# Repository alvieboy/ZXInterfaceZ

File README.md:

# ZX Interface Z

Interface Z - an expansion card for the ZX Spectrum which supports

- VGA Output
- USB devices such as joysticks, flash drives and keyboards
- Networking and Wifi
- Micro SD Card
- YM2149 audio

_Project status: Currently under development and only suitable for people that want
to help out with development and testing._

Current version is _ALPHA1_.

See [FEATURES](docs/FEATURES.md) for more details on the _ZX Interface Z_ features.
[(click here for PDF document)](docs/FEATURES.md.pdf)

# Overview

Block diagram of Interface Z [diagram](https://raw.githubusercontent.com/alvieboy/ZXInterfaceZ/master/docs/overview2.png)

# Models supported

The following models are supported:

- ZX Spectrum 16K
- ZX Spectrum 48K
- ZX Spectrum 128K (gray)
- ZX Spectrum 128K (toastrack)
- ZX Spectrum +2A
- ZX Spectrum +3

## Hardware
This section refers to the schematics and printed circuit board design of the Interface Z.
The digital design on the FPGA is described in the [FPGA design] section.
### Licensing
Schematics and PCB are released under [CC-BY-SA 2.0](https://creativecommons.org/licenses/by-sa/2.0/). This applies to all versions of the schematics and PCBs.
### Version
Current hardware version is 2.4. This is a pre-production version, not intented for general public availability.

## FPGA design
The FPGA design is written primarly in VHDL, targeting an Altera/Intel Cyclone IV device (EP4CE6E22C8N). There is no flash to store bitfile contents - the FPGA bitfile is loaded by the ESP32 MCU and stored inside the ESP32 flash.

### Licensing
Unless otherwise stated in each HDL or design support file, the FPGA design files are released under [BSD 3-Clause License](https://opensource.org/licenses/BSD-3-Clause).

## Firmware
This section applies to the firmware running on the ESP32 MCU.
### Licensing
Unless otherwise stated in each source support file, the firmware source files are released under [GPL version 3](https://opensource.org/licenses/GPL-3.0) license.

## Software
This section applies to the software intended to run on a separate computer (such as a PC, Mac or other).
### Licensing
Unless otherwise stated in each source support file, the software source files are released under [GPL version 3](https://opensource.org/licenses/GPL-3.0) license.

# Developing

See [DEVELOPING](docs/DEVELOPING.md) for development information regarding _ZX Interface Z_ 
[(click here for PDF document)](docs/DEVELOPING.md.pdf)

See [USER GUIDE](docs/USER_GUIDE.md) for build instructions.

# More information

- Follow the project on [Facebook - ZX Interface Z](https://www.facebook.com/zxinterfacez)
- Watch a [Demo of "Interface Z" for ZX Spectrum](https://www.youtube.com/watch?v=lMPc_8UKx1o) on YouTube

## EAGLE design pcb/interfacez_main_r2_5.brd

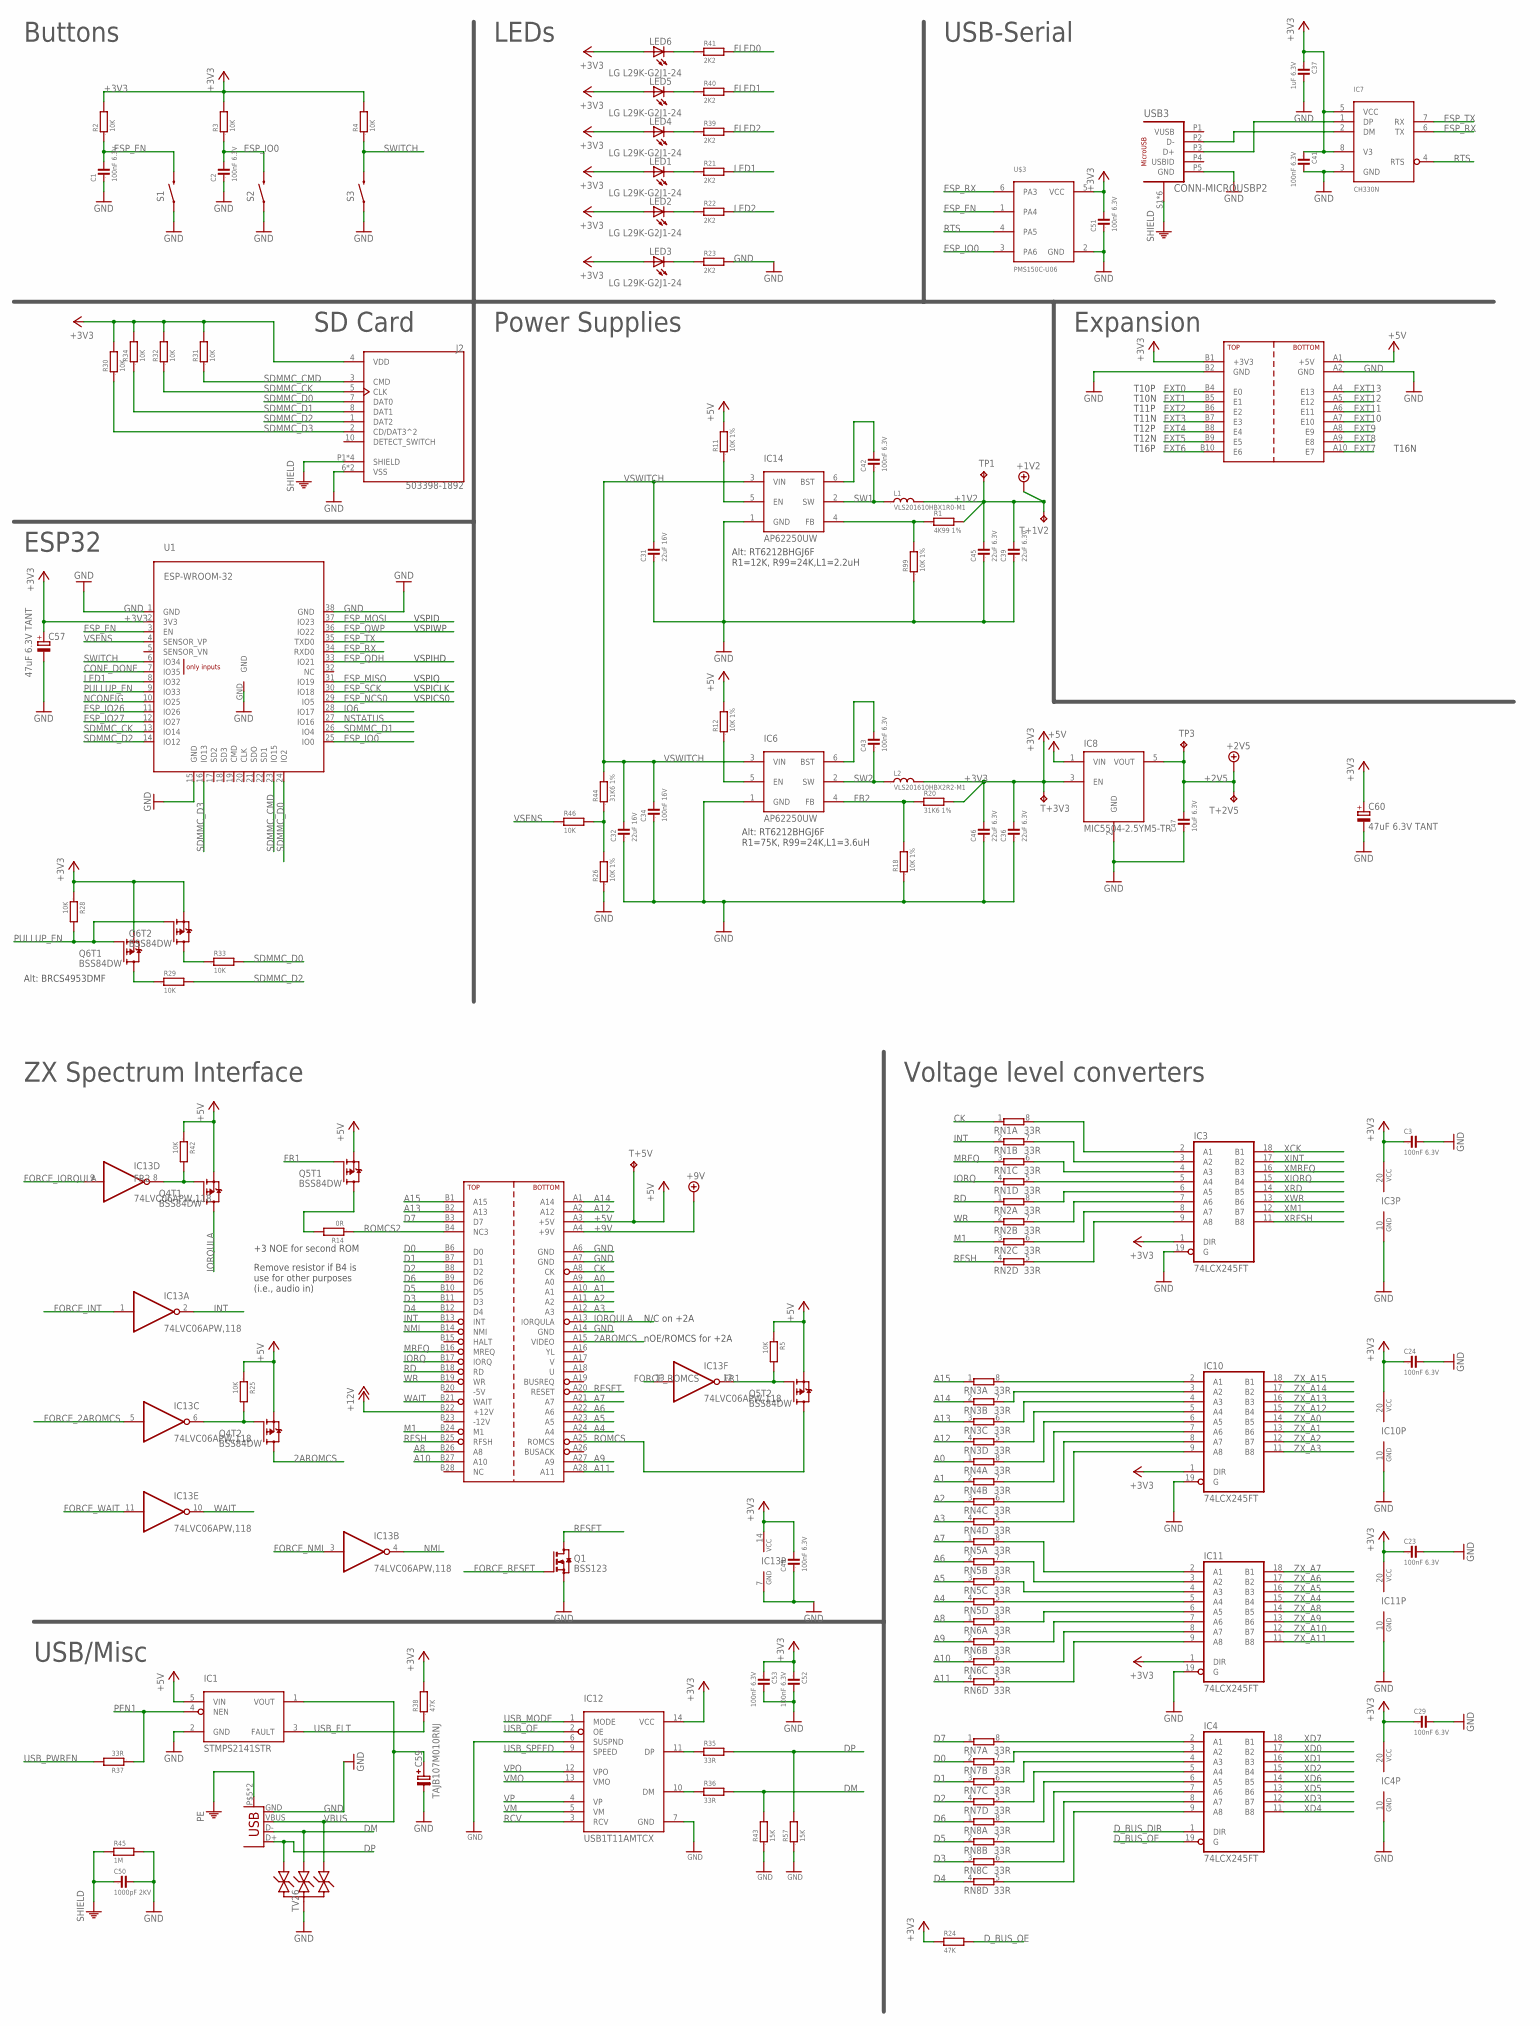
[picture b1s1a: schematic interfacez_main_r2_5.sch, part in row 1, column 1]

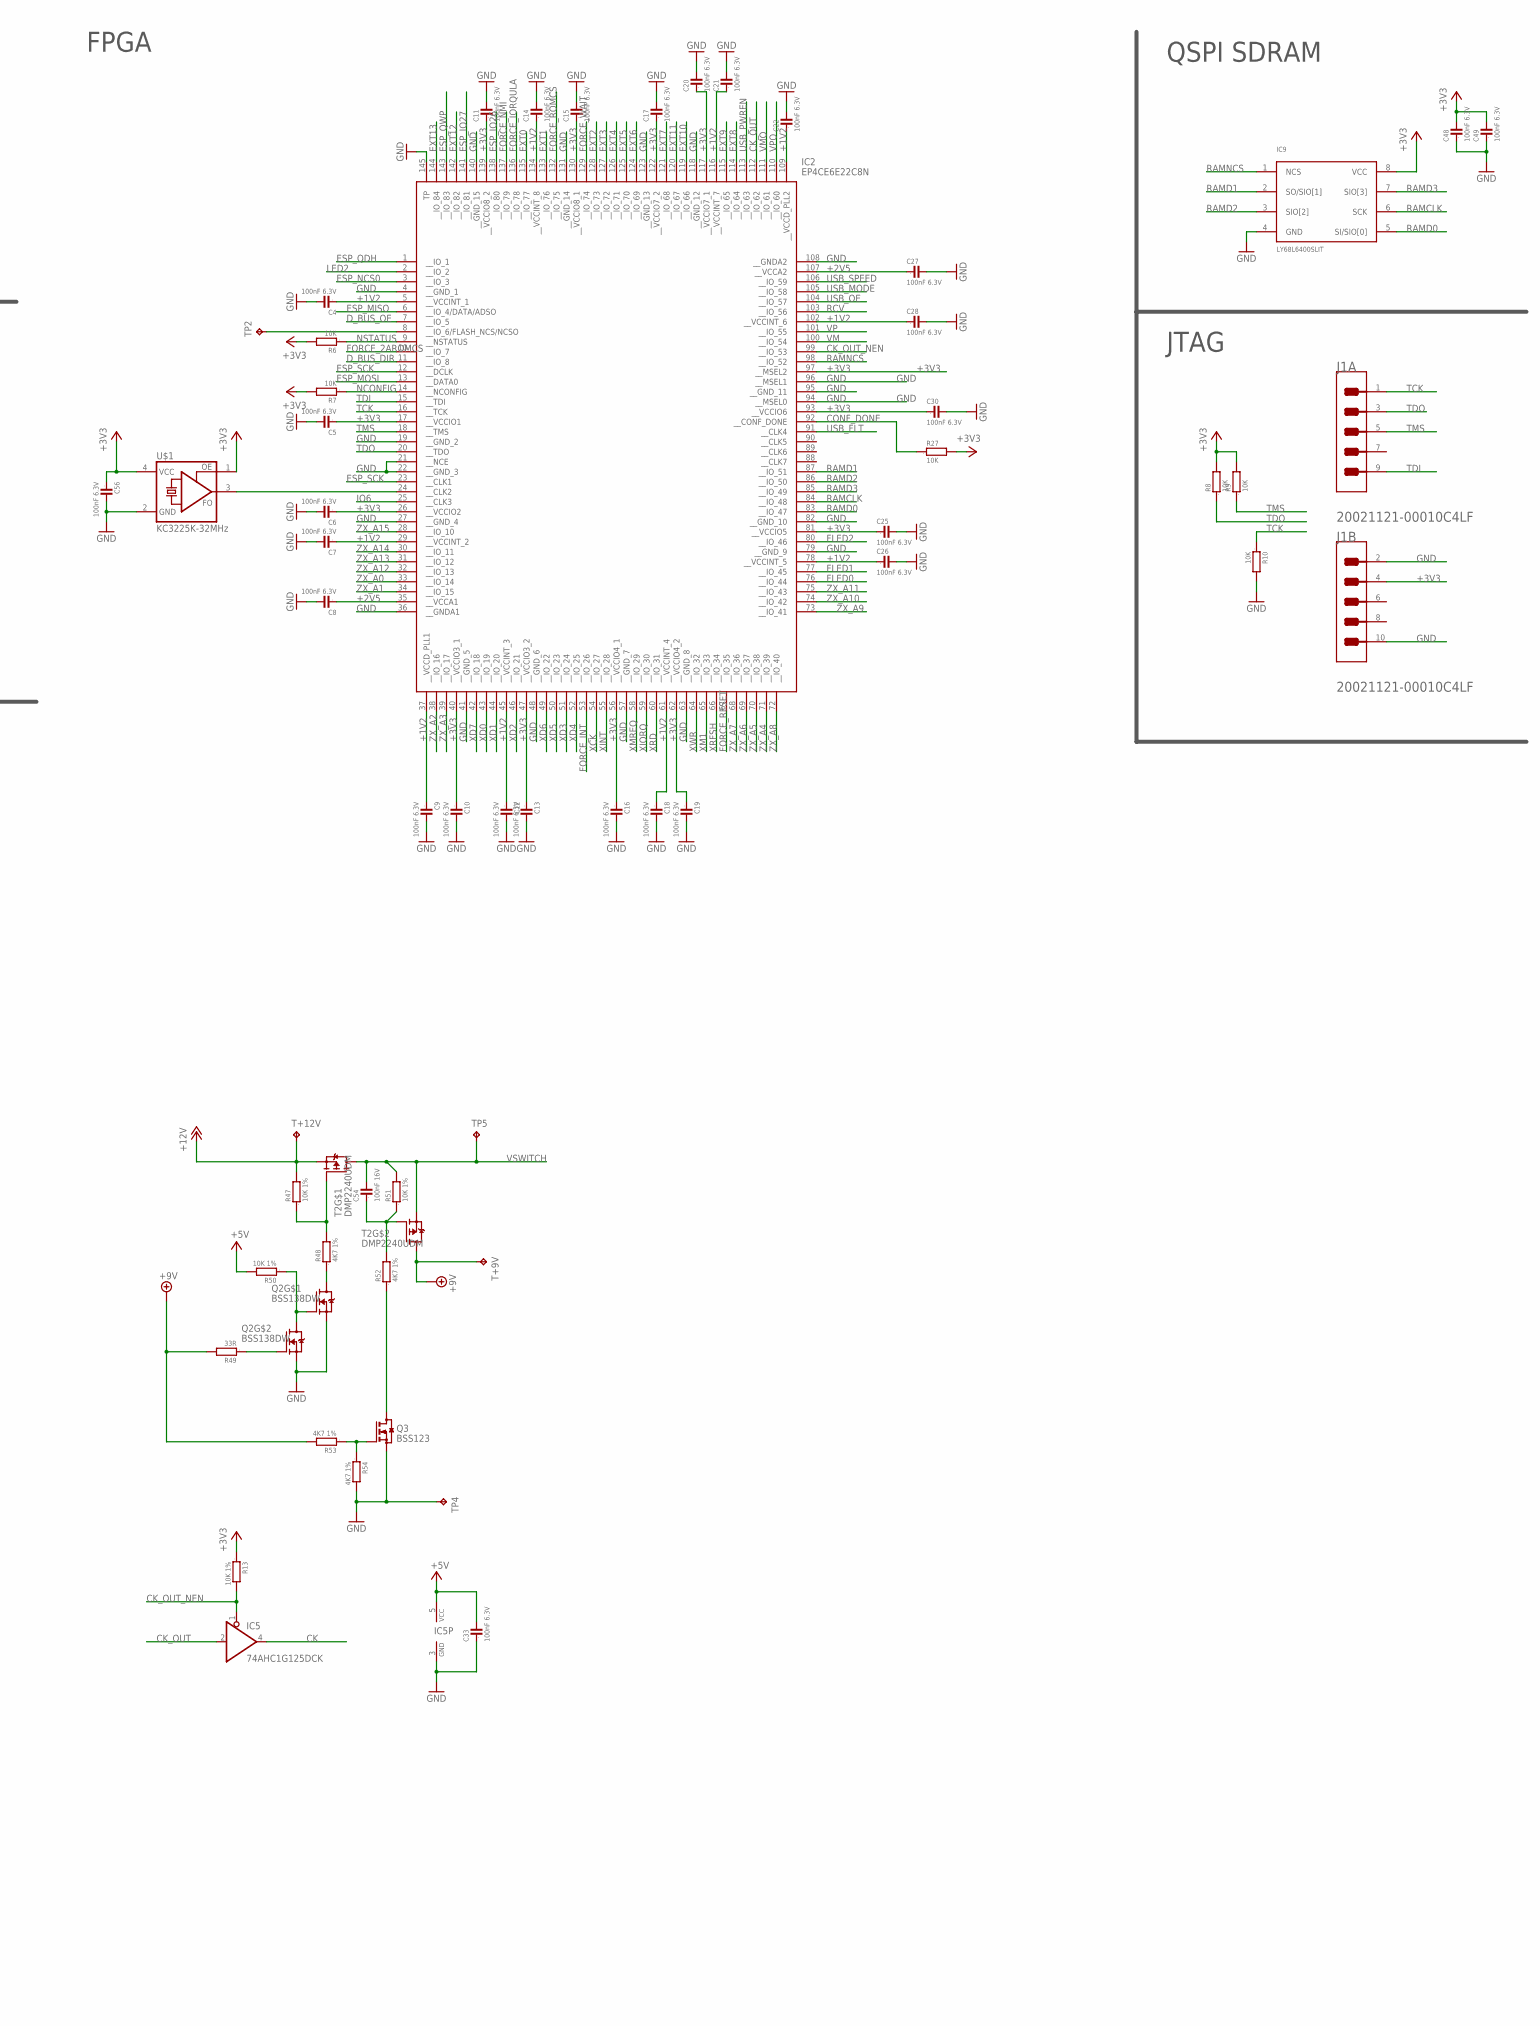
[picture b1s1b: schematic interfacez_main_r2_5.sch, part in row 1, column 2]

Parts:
C1, C2, C3, C4, C5, C6, C7, C8, C9, C10, C11, C12, C13, C14, C15, C16, C17, C18, C19, C20, C21, C22, C23, C24, C25, C26, C27, C28, C29, C30, C33, C40, C41, C42, C43, C48, C49, C51, C52, C53, C56: 100nF 6.3V; 0603
C31, C32: 22uF 16V; 1210
C34, C54: 100nF 16V; 0603
C36, C39, C45, C46: 22uF 6.3V; 0805
C37: 1uF 6.3V; 0603
C47: 10uF 6.3V; 0805
C50: 1000pF 2KV; 1210
C57, C60: 47uF 6.3V TANT; TANT_CASE_A
C59: TAJB107M010RNJ; TE-B-3528
CONN1: ZX_EDGE_DAUGHTERBOARD; ZX-EDGE-DAUGHTERBOARD
IC1: STMPS2141STR; SOT23-5L
IC2: EP4CE6E22C8N; QFP50P2200X2200X165-145N
IC3, IC4, IC10, IC11: 74LCX245FT; TSSOP20
IC5: 74AHC1G125DCK; SC70-5
IC6, IC14: AP62250UW; SOT23-6
IC7: CH330N; SOIC8
IC8: MIC5504-2.5YM5-TR; SOT23-5L
IC9: LY68L6400SLIT; SOIC8
IC12: USB1T11AMTCX; TSSOP14
IC13: 74LVC06APW,118; TSSOP14
J1: AMPHENOL_ICC_-_FCI_20021121-00010C4LFAMPHENOL_ICC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; AMPHENOL_ICC_-_FCI_20021121-00010C4LF_0
J2: 503398-1892; MOLEX_503398-1892
L1: VLS201610HBX1R0-M1; IND_0806
L2: VLS201610HBX2R2-M1; IND_0806
LED1, LED2, LED3, LED4, LED5, LED6: LG L29K-G2J1-24; LED-603
Q1, Q3: BSS123; SOT23
Q2: BSS138DW; SOT363_INFINEON
Q4, Q5, Q6: BSS84DW; SOT363_INFINEON
R1: 4K99 1%; 0603
R2, R3, R4, R5, R6, R7, R8, R9, R10, R25, R27, R28, R29, R30, R31, R32, R33, R34, R42, R46: 10K; 0603
R11, R12, R13, R18, R26, R47, R50, R51, R99: 10K 1%; 0603
R14: 0R; 0603
R20, R44: 31K6 1%; 0603
R21, R22, R23, R39, R40, R41: 2K2; 0603
R24, R38: 47K; 0603
R35, R36, R37, R49: 33R; 0603
R43, R57: 15K; 0603
R45: 1M; 0805
R48, R52, R53, R54: 4K7 1%; 0603
RN1, RN2, RN3, RN4, RN5, RN6, RN7, RN8: 33R; EXB28V
S1, S2, S3: SWITCHES_SMD-4; TACTILE_SWITCH_TALL
T2: DMP2240UDM; SOT23-6
T+1V2, T+2V5, T+3V3, T+5V, T+9V, T+12V: TPTP12SQ; TP12SQ
TP1, TP3: TPTP12R; TP12R
TP2, TP5: TPTP12SQ; TP12SQ
TP4: TPPAD1-13; P1-13
TV26: SP0503BAHT; SP0503
U1: ESP-WROOM-32
U$1: KC3225K-32MHz; KC3225K
U$3: PMS150C-U06; SOT23-6
U$5: INTERFACEZ_EDGEDAUGHTER; INTERFACEZ_EXPANSION_DAUGHTERCARD
USB2: USB-A-H
USB3: CONN-MICROUSBP2; MICROUSB_SMD_TH_7.5MM_4.85MM

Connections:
2AROMCS: CONN1.A15 (VIDEO), Q4.6 (D)
+1V2: C4.1, C7.1, C9.1, C12.1, C14.1, C18.1, C21.1, C22.1, C26.1, C28.1, C39.2, C45.2, IC2.5 (__VCCINT_1), IC2.29 (__VCCINT_2), IC2.37 (__VCCD_PLL1), IC2.45 (__VCCINT_3), IC2.61 (__VCCINT_4), IC2.78 (__VCCINT_5), IC2.102 (__VCCINT_6), IC2.109 (__VCCD_PLL2), IC2.116 (__VCCINT_7), IC2.134 (__VCCINT_8), L1.P$2 (2), R1.2, T+1V2.TP, TP1.TP
+2V5: C8.1, C27.1, C47.2, IC2.35 (__VCCA1), IC2.107 (__VCCA2), IC8.5 (VOUT), T+2V5.TP, TP3.TP
+3V3: C3.1, C5.1, C6.1, C10.1, C11.1, C13.1, C15.1, C16.1, C17.1, C19.1, C20.1, C23.1, C24.1, C25.1, C29.1, C30.1, C36.2, C37.1, C40.2, C41.1, C46.2, C48.2, C49.2, C51.2, C52.1, C53.1, C56.1, C57.PLUS (+), C60.PLUS (+), IC2.17 (__VCCIO1), IC2.26 (__VCCIO2), IC2.40 (__VCCIO3_1), IC2.47 (__VCCIO3_2), IC2.56 (__VCCIO4_1), IC2.62 (__VCCIO4_2), IC2.81 (__VCCIO5), IC2.93 (__VCCIO6), IC2.97 (__MSEL2), IC2.117 (__VCCIO7_1), IC2.122 (__VCCIO7_2), IC2.130 (__VCCIO8_1), IC2.139 (__VCCIO8_2), IC3.1 (DIR), IC3.20 (VCC), IC4.20 (VCC), IC7.5 (VCC), IC7.8 (V3), IC8.3 (EN), IC9.8 (VCC), IC10.1 (DIR), IC10.20 (VCC), IC11.1 (DIR), IC11.20 (VCC), IC12.14 (VCC), IC13.14 (VCC), J1.4, J2.4 (VDD), L2.P$2 (2), LED1.A, LED2.A, LED3.A, LED4.A, LED5.A, LED6.A, Q6.1 (S), Q6.4 (S), R2.2, R3.2, R4.2, R6.2, R7.2, R8.2, R9.2, R13.1, R20.2, R24.1, R27.2, R28.1, R30.2, R31.2, R32.2, R34.2, R38.2, T+3V3.TP, U1.2 (3V3), U$1.1 (OE), U$1.4 (VCC), U$3.5 (VCC), U$5.B1 (+3V3)
+5V: C33.2, CONN1.A3 (+5V), IC1.5 (VIN), IC5.5 (VCC), IC8.1 (VIN), Q4.1 (S), Q4.4 (S), Q5.1 (S), Q5.4 (S), R5.1, R11.2, R12.2, R25.1, R42.1, R50.2, T+5V.TP, U$5.A1 (+5V)
+9V: CONN1.A4 (+9V), R49.2, R53.2, T2.4 (D), T+9V.TP
+12V: CONN1.B22 (+12V), R47.2, T2.5 (S), T+12V.TP
-5V: CONN1.B20 (-5V)
-12V: CONN1.B23 (-12V)
A0: CONN1.A9 (A0), RN4.1
A1: CONN1.A10 (A1), RN4.2 (1)
A2: CONN1.A11 (A2), RN4.3 (1)
A3: CONN1.A12 (A3), RN4.4 (1)
A4: CONN1.A24 (A4), RN5.4 (1)
A5: CONN1.A23 (A5), RN5.3 (1)
A6: CONN1.A22 (A6), RN5.2 (1)
A7: CONN1.A21 (A7), RN5.1
A8: CONN1.B26 (A8), RN6.1
A9: CONN1.A27 (A9), RN6.2 (1)
A10: CONN1.B27 (A10), RN6.3 (1)
A11: CONN1.A28 (A11), RN6.4 (1)
A12: CONN1.A2 (A12), RN3.4 (1)
A13: CONN1.B2 (A13), RN3.3 (1)
A14: CONN1.A1 (A14), RN3.2 (1)
A15: CONN1.B1 (A15), RN3.1
CK: CONN1.A8 (CK), IC5.4 (O), RN1.1
CK_OUT: IC2.112 (__IO_62), IC5.2 (I)
CK_OUT_NEN: IC2.99 (__IO_53), IC5.1 (OE), R13.2
CONF_DONE: IC2.92 (__CONF_DONE), R27.1, U1.7 (IO35)
D0: CONN1.B6 (D0), RN7.2 (1)
D1: CONN1.B7 (D1), RN7.3 (1)
D2: CONN1.B8 (D2), RN7.4 (1)
D3: CONN1.B11 (D3), RN8.3 (1)
D4: CONN1.B12 (D4), RN8.4 (1)
D5: CONN1.B10 (D5), RN8.2 (1)
D6: CONN1.B9 (D6), RN8.1
D7: CONN1.B3 (D7), RN7.1
DM: R36.2, R43.2, TV26.3 (B), USB2.D-
DP: R35.2, R57.2, TV26.2 (A), USB2.D+
D_BUS_DIR: IC2.11 (__IO_8), IC4.1 (DIR)
D_BUS_OE: IC2.7 (__IO_5), IC4.19 (G), R24.2
ESP_EN: C1.2, R2.1, S1.B2 (2), U1.3 (EN), U$3.1 (PA4)
ESP_IO0: C2.2, R3.1, S2.B2 (2), U1.25 (IO0), U$3.3 (PA6)
ESP_IO26: IC2.138 (__IO_80), U1.11 (IO26)
ESP_IO27: IC2.141 (__IO_81), U1.12 (IO27)
ESP_MISO: IC2.6 (__IO_4/DATA/ADSO), U1.31 (IO19)
ESP_MOSI: IC2.13 (__DATA0), U1.37 (IO23)
ESP_NCS0: IC2.3 (__IO_3), U1.29 (IO5)
ESP_QDH: IC2.1 (__IO_1), U1.33 (IO21)
ESP_QWP: IC2.143 (__IO_83), U1.36 (IO22)
ESP_RX: IC7.6 (TX), U1.34 (RXD0), U$3.6 (PA3)
ESP_SCK: IC2.12 (__DCLK), IC2.23 (__CLK1), U1.30 (IO18)
ESP_TX: IC7.7 (RX), U1.35 (TXD0)
EXT0: IC2.135 (__IO_77), U$5.B4 (E0)
EXT1: IC2.133 (__IO_76), U$5.B5 (E1)
EXT2: IC2.128 (__IO_73), U$5.B6 (E2)
EXT3: IC2.127 (__IO_72), U$5.B7 (E3)
EXT4: IC2.126 (__IO_71), U$5.B8 (E4)
EXT5: IC2.125 (__IO_70), U$5.B9 (E5)
EXT6: IC2.124 (__IO_69), U$5.B10 (E6)
EXT7: IC2.121 (__IO_68), U$5.A10 (E7)
EXT8: IC2.114 (__IO_64), U$5.A9 (E8)
EXT9: IC2.115 (__IO_65), U$5.A8 (E9)
EXT10: IC2.119 (__IO_66), U$5.A7 (E10)
EXT11: IC2.120 (__IO_67), U$5.A6 (E11)
EXT12: IC2.142 (__IO_82), U$5.A5 (E12)
EXT13: IC2.144 (__IO_84), U$5.A4 (E13)
FB2: IC6.4 (FB), R18.2, R20.1
FLED0: IC2.76 (__IO_44), R41.2
FLED1: IC2.77 (__IO_45), R40.2
FLED2: IC2.80 (__IO_46), R39.2
FORCE_2AROMCS: IC2.10 (__IO_7), IC13.5 (I)
FORCE_INT: IC2.53 (__IO_26), IC13.1 (I)
FORCE_IORQULA: IC2.136 (__IO_78), IC13.9 (I)
FORCE_NMI: IC2.137 (__IO_79), IC13.3 (I)
FORCE_RESET: IC2.67 (__IO_35), Q1.1 (G)
FORCE_ROMCS: IC2.132 (__IO_75), IC13.13 (I)
FORCE_WAIT: IC2.129 (__IO_74), IC13.11 (I)
FR1: IC13.12 (O), Q5.2 (G), Q5.5 (G), R5.2
FR2: IC13.8 (O), Q4.5 (G), R42.2
GND: C1.1, C2.1, C3.2, C4.2, C5.2, C6.2, C7.2, C8.2, C9.2, C10.2, C11.2, C12.2, C13.2, C14.2, C15.2, C16.2, C17.2, C18.2, C19.2, C20.2, C21.2, C22.2, C23.2, C24.2, C25.2, C26.2, C27.2, C28.2, C29.2, C30.2, C31.1, C32.1, C33.1, C34.1, C36.1, C37.2, C39.1, C40.1, C41.2, C45.1, C46.1, C47.1, C48.1, C49.1, C50.2, C51.1, C52.2, C53.2, C56.2, C57.MINUS (-), C59.-, C60.MINUS (-), CONN1.A6 (GND), CONN1.A7 (GND), CONN1.A14 (GND), IC1.2 (GND), IC2.4 (__GND_1), IC2.19 (__GND_2), IC2.21 (__NCE), IC2.22 (__GND_3), IC2.27 (__GND_4), IC2.36 (__GNDA1), IC2.41 (__GND_5), IC2.48 (__GND_6), IC2.57 (__GND_7), IC2.63 (__GND_8), IC2.79 (__GND_9), IC2.82 (__GND_10), IC2.94 (__MSEL0), IC2.95 (__GND_11), IC2.96 (__MSEL1), IC2.108 (__GNDA2), IC2.118 (__GND_12), IC2.123 (__GND_13), IC2.131 (__GND_14), IC2.140 (__GND_15), IC2.145 (TP), IC3.10 (GND), IC3.19 (G), IC4.10 (GND), IC5.3 (GND), IC6.1 (GND), IC7.3 (GND), IC8.2 (GND), IC9.4 (GND), IC10.10 (GND), IC10.19 (G), IC11.10 (GND), IC11.19 (G), IC12.6 (SUSPND), IC12.7 (GND), IC13.7 (GND), IC14.1 (GND), J1.2, J1.10, J2.6 (VSS), J2.9 (VSS), Q1.2 (S), Q2.1 (S), Q2.4 (S), Q3.2 (S), R10.2, R18.1, R23.2, R26.1, R43.1, R45.2, R54.2, R57.1, R99.1, S1.A2 (1), S2.A2 (1), S3.A2 (1), TP4.TP, TV26.1 (COM), U1.1 (GND), U1.15 (GND), U1.38 (GND), U1.GND, U$1.2 (GND), U$3.2 (GND), U$5.A2 (GND), U$5.B2 (GND), USB2.GND, USB3.P5 (GND)
INT: CONN1.B13 (INT), IC13.2 (O), RN1.2 (1)
IO6: IC2.25 (__CLK3), U1.28 (IO17)
IORQ: CONN1.B17 (IORQ), RN1.4 (1)
IORQULA: CONN1.A13 (IORQULA), Q4.3 (D)
LED1: R21.2, U1.8 (IO32)
LED2: IC2.2 (__IO_2), R22.2
M1: CONN1.B24 (M1), RN2.3 (1)
MREQ: CONN1.B16 (MREQ), RN1.3 (1)
unnamed: Q5.3 (D), R14.2
unnamed: LED1.C, R21.1
unnamed: LED2.C, R22.1
unnamed: LED3.C, R23.1
unnamed: R47.1, R48.2, T2.1 (G)
unnamed: Q2.3 (D), R48.1
unnamed: IC3.2 (A1), RN1.8 (2)
unnamed: IC3.3 (A2), RN1.7 (2)
unnamed: IC10.2 (A1), RN3.8 (2)
unnamed: IC10.3 (A2), RN3.7 (2)
unnamed: IC10.4 (A3), RN3.6 (2)
unnamed: IC10.5 (A4), RN3.5 (2)
unnamed: IC2.24 (__CLK2), U$1.3 (FO)
unnamed: IC10.6 (A5), RN4.8 (2)
unnamed: IC10.7 (A6), RN4.7 (2)
unnamed: IC4.2 (A1), RN7.8 (2)
unnamed: IC4.3 (A2), RN7.7 (2)
unnamed: IC10.8 (A7), RN4.6 (2)
unnamed: IC2.8 (__IO_6/FLASH_NCS/NCSO), TP2.TP
unnamed: LED4.C, R39.1
unnamed: C43.2, IC6.6 (BST)
unnamed: IC10.9 (A8), RN4.5 (2)
unnamed: IC11.2 (A1), RN5.8 (2)
unnamed: IC11.3 (A2), RN5.7 (2)
unnamed: IC11.4 (A3), RN5.6 (2)
unnamed: IC11.5 (A4), RN5.5 (2)
unnamed: IC11.6 (A5), RN6.8 (2)
unnamed: IC11.7 (A6), RN6.7 (2)
unnamed: IC11.8 (A7), RN6.6 (2)
unnamed: IC11.9 (A8), RN6.5 (2)
unnamed: IC4.4 (A3), RN7.6 (2)
unnamed: IC4.5 (A4), RN7.5 (2)
unnamed: IC4.6 (A5), RN8.8 (2)
unnamed: IC4.7 (A6), RN8.7 (2)
unnamed: IC4.8 (A7), RN8.6 (2)
unnamed: IC4.9 (A8), RN8.5 (2)
unnamed: IC3.4 (A3), RN1.6 (2)
unnamed: IC3.5 (A4), RN1.5 (2)
unnamed: IC3.6 (A5), RN2.8 (2)
unnamed: IC3.7 (A6), RN2.7 (2)
unnamed: IC3.8 (A7), RN2.6 (2)
unnamed: IC3.9 (A8), RN2.5 (2)
unnamed: C42.2, IC14.6 (BST)
unnamed: IC6.5 (EN), R12.1
unnamed: IC14.4 (FB), R1.1, R99.2
unnamed: IC14.5 (EN), R11.1
unnamed: IC13.6 (O), Q4.2 (G), R25.2
unnamed: Q6.3 (D), R29.1
unnamed: LED5.C, R40.1
unnamed: LED6.C, R41.1
unnamed: IC12.11 (DP), R35.1
unnamed: IC12.10 (DM), R36.1
unnamed: Q2.5 (G), Q2.6 (D), R50.1
unnamed: Q6.6 (D), R33.1
unnamed: Q2.2 (G), R49.1
unnamed: C54.1, R51.1, R52.2, T2.3 (G)
unnamed: Q3.1 (G), R53.1, R54.1
unnamed: Q3.3 (D), R52.1
unnamed: IC7.1 (DP), USB3.P3 (D+)
unnamed: IC7.2 (DM), USB3.P2 (D-)
NCONFIG: IC2.14 (__NCONFIG), R7.1, U1.10 (IO25)
NMI: CONN1.B14 (NMI), IC13.4 (O)
NSTATUS: IC2.9 (__NSTATUS), R6.1, U1.27 (IO16)
PE: C50.1, J2.P1 (SHIELD), J2.P2 (SHIELD), J2.P3 (SHIELD), J2.P4 (SHIELD), R45.1, USB2.P$5 (SHIELD), USB2.P$6 (SHIELD), USB3.S1 (SHIELD), USB3.S2 (SHIELD), USB3.S3 (SHIELD), USB3.S4 (SHIELD), USB3.S5 (SHIELD), USB3.S6 (SHIELD)
PEN1: IC1.4 (NEN), R37.1
PULLUP_EN: Q6.2 (G), Q6.5 (G), R28.2, U1.9 (IO33)
RAMCLK: IC2.84 (__IO_48), IC9.6 (SCK)
RAMD0: IC2.83 (__IO_47), IC9.5 (SI/SIO[0])
RAMD1: IC2.87 (__IO_51), IC9.2 (SO/SIO[1])
RAMD2: IC2.86 (__IO_50), IC9.3 (SIO[2])
RAMD3: IC2.85 (__IO_49), IC9.7 (SIO[3])
RAMNCS: IC2.98 (__IO_52), IC9.1 (NCS)
RCV: IC2.103 (__IO_56), IC12.3 (RCV)
RD: CONN1.B18 (RD), RN2.1
RESET: CONN1.A20 (RESET), Q1.3 (D)
RFSH: CONN1.B25 (RFSH), RN2.4 (1)
ROMCS: CONN1.A25 (ROMCS), Q5.6 (D)
ROMCS2: CONN1.B4 (NC3), R14.1
RTS: IC7.4 (RTS), U$3.4 (PA5)
SDMMC_CK: J2.5 (CLK), R32.1, U1.13 (IO14)
SDMMC_CMD: J2.3 (CMD), R31.1, U1.23 (IO15)
SDMMC_D0: J2.7 (DAT0), R33.2, U1.24 (IO2)
SDMMC_D1: J2.8 (DAT1), R34.1, U1.26 (IO4)
SDMMC_D2: J2.1 (DAT2), R29.2, U1.14 (IO12)
SDMMC_D3: J2.2 (CD/DAT3^2), R30.1, U1.16 (IO13)
SW1: C42.1, IC14.2 (SW), L1.P$1 (1)
SW2: C43.1, IC6.2 (SW), L2.P$1 (1)
SWITCH: R4.1, S3.B2 (2), U1.6 (IO34)
TCK: IC2.16 (__TCK), J1.1, R10.1
TDI: IC2.15 (__TDI), J1.9
TDO: IC2.20 (__TDO), J1.3, R8.1
TMS: IC2.18 (__TMS), J1.5, R9.1
USB_FLT: IC1.3 (FAULT), IC2.91 (__CLK4), R38.1
USB_MODE: IC2.105 (__IO_58), IC12.1 (MODE)
USB_OE: IC2.104 (__IO_57), IC12.2 (OE)
USB_PWREN: IC2.113 (__IO_63), R37.2
USB_SPEED: IC2.106 (__IO_59), IC12.9 (SPEED)
VBUS: C59.+, IC1.1 (VOUT), TV26.4 (C), USB2.VBUS
VDIV: R26.2, R44.1, R46.2
VM: IC2.100 (__IO_54), IC12.5 (VM)
VMO: IC2.111 (__IO_61), IC12.13 (VMO)
VP: IC2.101 (__IO_55), IC12.4 (VP)
VPO: IC2.110 (__IO_60), IC12.12 (VPO)
VSENS: R46.1, U1.4 (SENSOR_VP)
VSWITCH: C31.2, C32.2, C34.2, C54.2, IC6.3 (VIN), IC14.3 (VIN), R44.2, R51.2, T2.2 (S), T2.6 (D), TP5.TP
WAIT: CONN1.B21 (WAIT), IC13.10 (O)
WR: CONN1.B19 (WR), RN2.2 (1)
XCK: IC2.54 (__IO_27), IC3.18 (B1)
XD0: IC2.43 (__IO_19), IC4.17 (B2)
XD1: IC2.44 (__IO_20), IC4.16 (B3)
XD2: IC2.46 (__IO_21), IC4.15 (B4)
XD3: IC2.51 (__IO_24), IC4.12 (B7)
XD4: IC2.52 (__IO_25), IC4.11 (B8)
XD5: IC2.50 (__IO_23), IC4.13 (B6)
XD6: IC2.49 (__IO_22), IC4.14 (B5)
XD7: IC2.42 (__IO_18), IC4.18 (B1)
XINT: IC2.55 (__IO_28), IC3.17 (B2)
XIORQ: IC2.59 (__IO_30), IC3.15 (B4)
XM1: IC2.65 (__IO_33), IC3.12 (B7)
XMREQ: IC2.58 (__IO_29), IC3.16 (B3)
XRD: IC2.60 (__IO_31), IC3.14 (B5)
XRFSH: IC2.66 (__IO_34), IC3.11 (B8)
XWR: IC2.64 (__IO_32), IC3.13 (B6)
ZX_A0: IC2.33 (__IO_14), IC10.14 (B5)
ZX_A1: IC2.34 (__IO_15), IC10.13 (B6)
ZX_A2: IC2.38 (__IO_16), IC10.12 (B7)
ZX_A3: IC2.39 (__IO_17), IC10.11 (B8)
ZX_A4: IC2.71 (__IO_39), IC11.15 (B4)
ZX_A5: IC2.70 (__IO_38), IC11.16 (B3)
ZX_A6: IC2.69 (__IO_37), IC11.17 (B2)
ZX_A7: IC2.68 (__IO_36), IC11.18 (B1)
ZX_A8: IC2.72 (__IO_40), IC11.14 (B5)
ZX_A9: IC2.73 (__IO_41), IC11.13 (B6)
ZX_A10: IC2.74 (__IO_42), IC11.12 (B7)
ZX_A11: IC2.75 (__IO_43), IC11.11 (B8)
ZX_A12: IC2.32 (__IO_13), IC10.15 (B4)
ZX_A13: IC2.31 (__IO_12), IC10.16 (B3)
ZX_A14: IC2.30 (__IO_11), IC10.17 (B2)
ZX_A15: IC2.28 (__IO_10), IC10.18 (B1)

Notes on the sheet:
Buttons
SD Card
ESP32
LEDs
USB-Serial
Power Supplies
FPGA
QSPI SDRAM
ZX Spectrum Interface
Voltage level converters
USB/Misc
VSPICLK
VSPICS0
VSPIQ
VSPIWP
VSPIHD
VSPID
+3 NOE for second ROM
Alt: BRCS4953DMF
Expansion
T10P
T10N
T11P
T11N
T12P
T12N
T16P
T16N
JTAG
N/C on +2A
nOE/ROMCS for +2A
Remove resistor if B4 is use for other purposes (i.e., audio in)
Alt: RT6212BHGJ6F R1=12K, R99=24K,L1=2.2uH
Alt: RT6212BHGJ6F R1=75K, R99=24K,L1=3.6uH

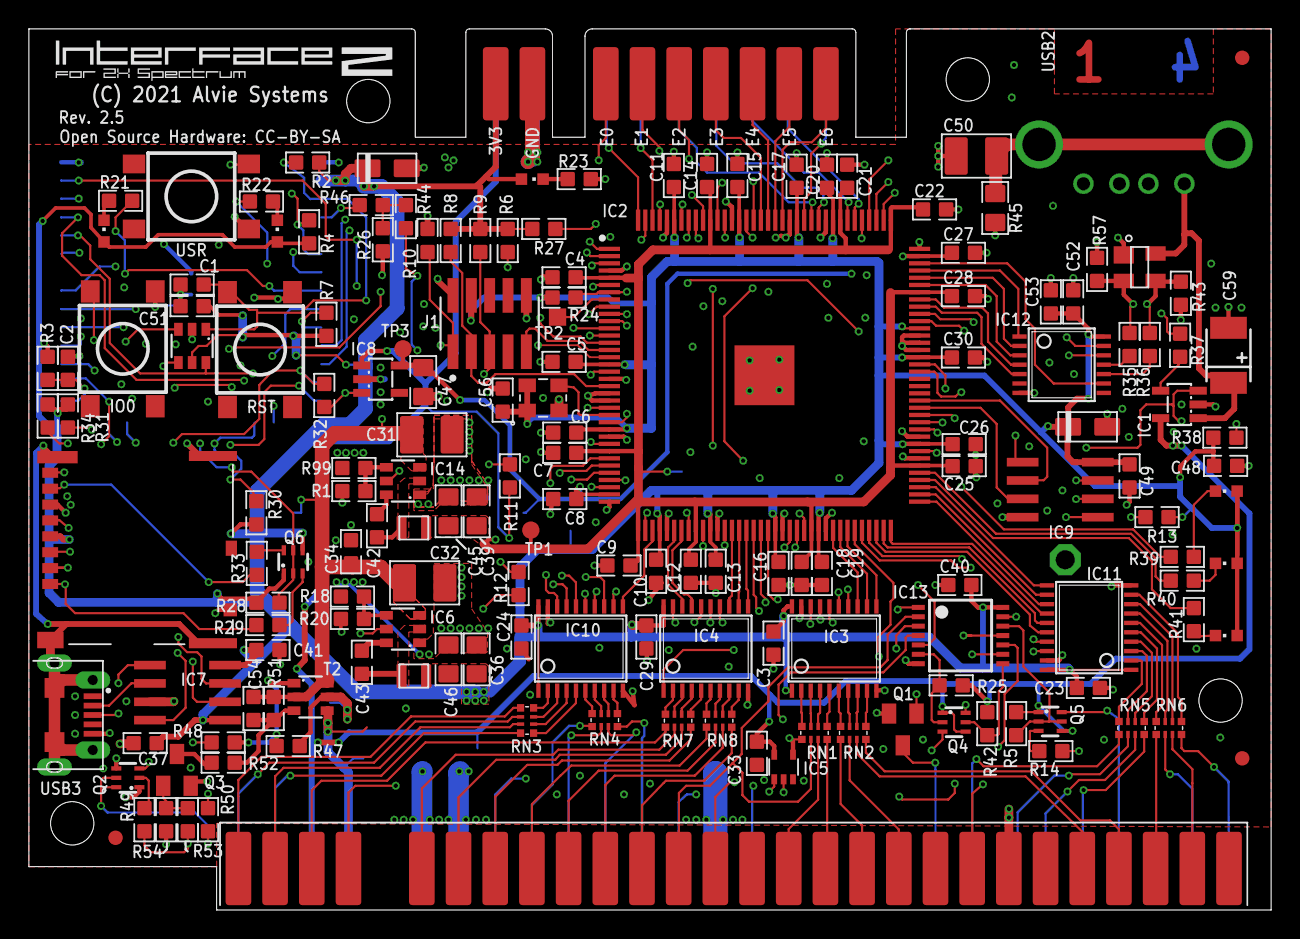
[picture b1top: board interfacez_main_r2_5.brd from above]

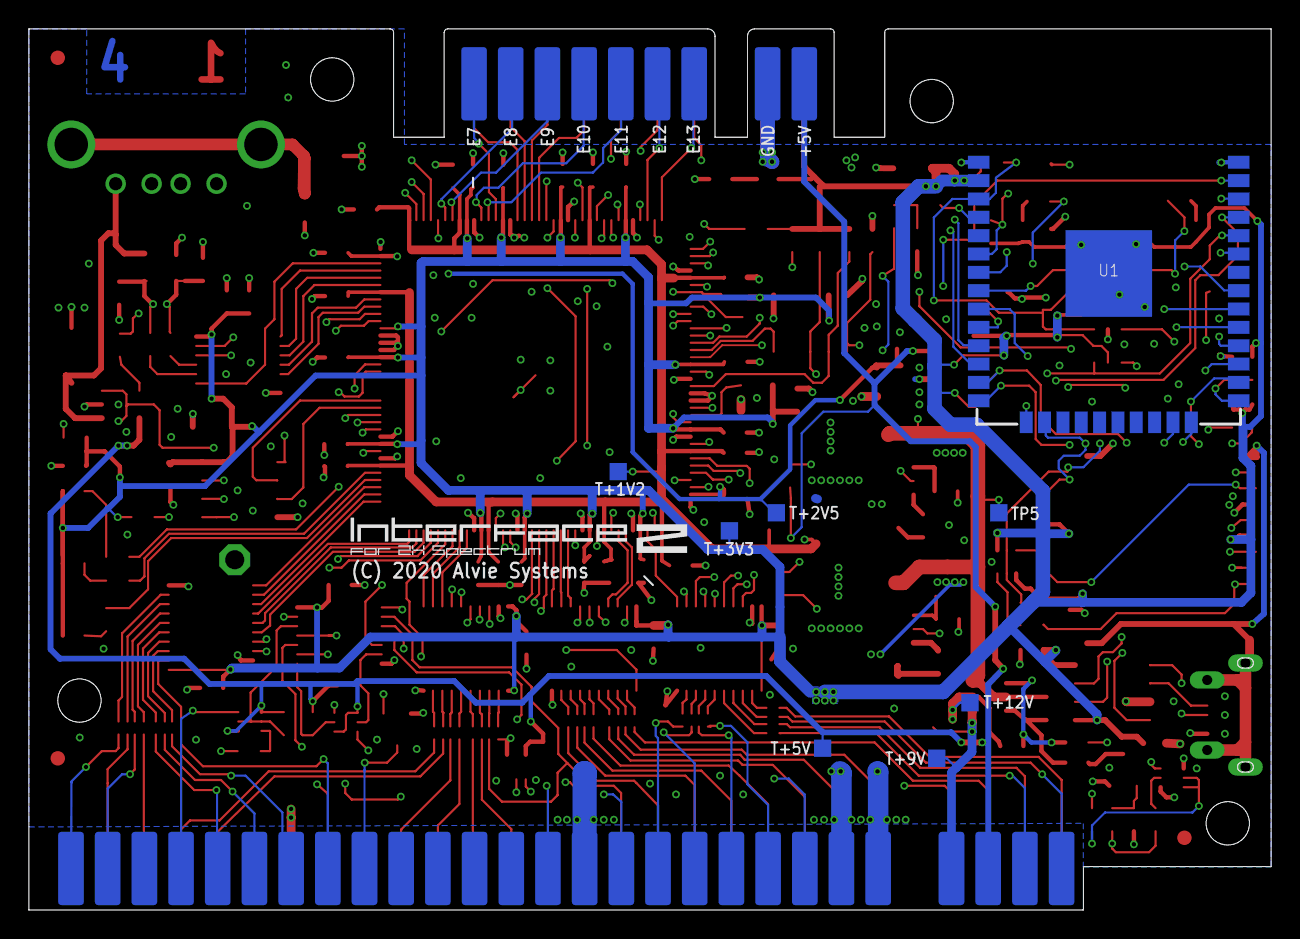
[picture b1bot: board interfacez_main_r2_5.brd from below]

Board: 4 copper layers, 86.0 x 61.0 mm, 171 parts (8 on the bottom side), 226 nets.

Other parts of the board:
U$6, U$8, U$9: FIDUCIAL_G10

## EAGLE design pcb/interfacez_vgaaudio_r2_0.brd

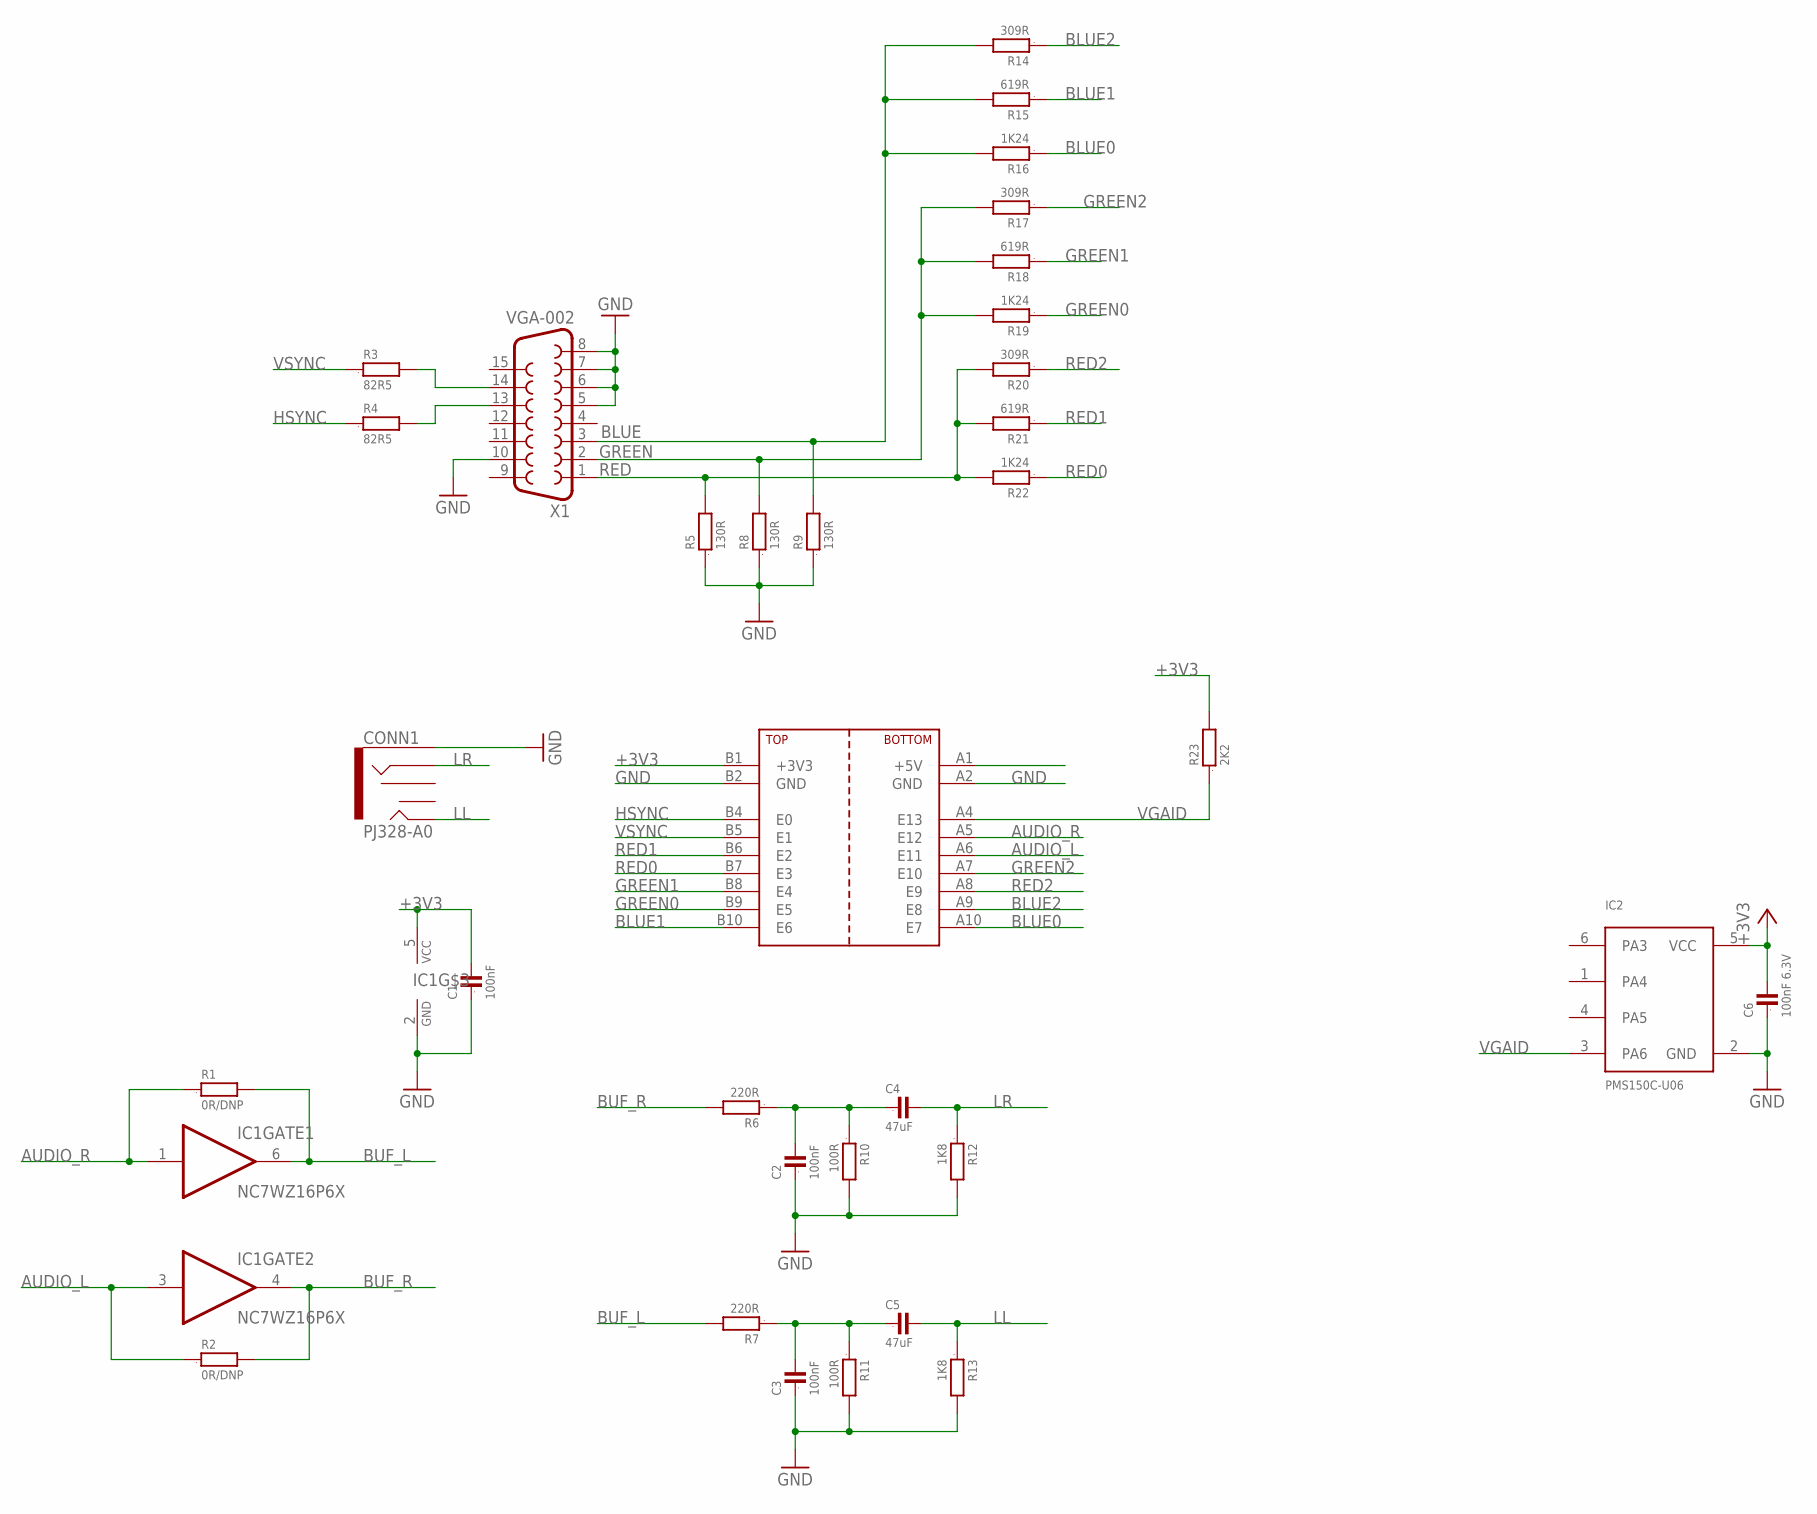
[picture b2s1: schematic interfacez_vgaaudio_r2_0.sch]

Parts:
C1, C2, C3: 100nF; 0603
C4, C5: 47uF; 1206
C6: 100nF 6.3V; 0603
CONN1: PJ328-A0; PJ328A0
IC1: NC7WZ16P6X; SC70-6
IC2: PMS150C-U06; SOT23-6
R1, R2: 0R/DNP; 0603
R3, R4: 82R5; 0603
R5, R8, R9: 130R; 0603
R6, R7: 220R; 0603
R10, R11: 100R; 0603
R12, R13: 1K8; 0603
R14, R17, R20: 309R; 0603
R15, R18, R21: 619R; 0603
R16, R19, R22: 1K24; 0603
R23: 2K2; 0603
U$1: INTERFACEZ_EDGEDAUGHTER; INTERFACEZ_EXPANSION_DAUGHTERCARD
X1: VGA-002; HDF15H

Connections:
+3V3: C1.2, C6.2, IC1.5 (VCC), IC2.5 (VCC), R23.2, U$1.B1 (+3V3)
AUDIO_L: IC1.3 (I), R2.1, U$1.A6 (E11)
AUDIO_R: IC1.1 (I), R1.1, U$1.A5 (E12)
BLUE: R9.2, R14.2, R15.2, R16.2, X1.3
BLUE0: R16.1, U$1.A10 (E7)
BLUE1: R15.1, U$1.B10 (E6)
BLUE2: R14.1, U$1.A9 (E8)
BUF_L: IC1.6 (O), R1.2, R7.2
BUF_R: IC1.4 (O), R2.2, R6.2
GND: C1.1, C2.1, C3.1, C6.1, CONN1.1 (SLEEVE), IC1.2 (GND), IC2.2 (GND), R5.1, R8.1, R9.1, R10.2, R11.2, R12.2, R13.2, U$1.A2 (GND), U$1.B2 (GND), X1.5, X1.6, X1.7, X1.8, X1.10
GREEN: R8.2, R17.2, R18.2, R19.2, X1.2
GREEN0: R19.1, U$1.B9 (E5)
GREEN1: R18.1, U$1.B8 (E4)
GREEN2: R17.1, U$1.A7 (E10)
HSYNC: R4.1, U$1.B4 (E0)
LL: C5.2, CONN1.2 (TIP), R13.1
LR: C4.2, CONN1.3 (RING), R12.1
unnamed: R4.2, X1.13
unnamed: R3.2, X1.14
unnamed: C3.2, C5.1, R7.1, R11.1
unnamed: C2.2, C4.1, R6.1, R10.1
RED: R5.2, R20.2, R21.2, R22.2, X1.1
RED0: R22.1, U$1.B7 (E3)
RED1: R21.1, U$1.B6 (E2)
RED2: R20.1, U$1.A8 (E9)
VGAID: IC2.3 (PA6), R23.1, U$1.A4 (E13)
VSYNC: R3.1, U$1.B5 (E1)

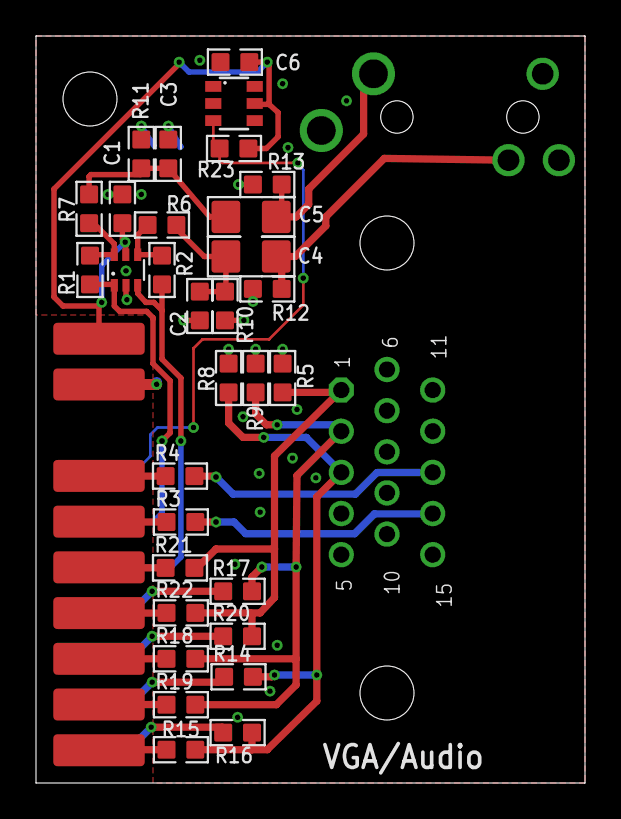
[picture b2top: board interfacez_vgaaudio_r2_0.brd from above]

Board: 3 copper layers, 30.5 x 41.5 mm, 35 parts (1 on the bottom side), 27 nets.

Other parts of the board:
U$14: LOGO-23-2.65

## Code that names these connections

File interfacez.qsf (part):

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set_location_assignment PIN_1 -to ESP_QHD_io
set_location_assignment PIN_2 -to LED2_o
set_location_assignment PIN_3 -to ESP_NCSO_i
set_location_assignment PIN_6 -to ESP_MISO_io
set_location_assignment PIN_7 -to D_BUS_OE_o
set_location_assignment PIN_8 -to TP4_o
set_location_assignment PIN_10 -to A_BUS_OE_o
set_location_assignment PIN_11 -to D_BUS_DIR_o
set_location_assignment PIN_13 -to ESP_MOSI_io
set_location_assignment PIN_23 -to ESP_SCK_i
set_location_assignment PIN_24 -to CLK_i
set_location_assignment PIN_28 -to XA_i[15]
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set_location_assignment PIN_138 -to ESP_IO26_o
set_location_assignment PIN_141 -to ESP_IO27_o
set_location_assignment PIN_142 -to EXT_io[12]
set_location_assignment PIN_143 -to ESP_QWP_io
set_location_assignment PIN_144 -to EXT_io[13]
set_global_assignment -name CYCLONEII_RESERVE_NCEO_AFTER_CONFIGURATION "USE AS REGULAR IO"
set_global_assignment -name RESERVE_DATA0_AFTER_CONFIGURATION "USE AS REGULAR IO"
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

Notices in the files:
interfacez.qsf:
Copyright (C) 2019  Intel Corporation. All rights reserved.
pcb/interfacez_main_r2_5.brd:
(C) 2021 Alvie Systems
Open Source Hardware: CC-BY-SA
(C) 2020 Alvie Systems
parts and their libraries:
cap-pan40: Copyright (C) 2004, Bob Starr
dicons: Copyright (C) 2004, Bob Starr (rtzaudio@mindspring.com)
